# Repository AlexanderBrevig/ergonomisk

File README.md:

# Ergonomisk

My first ergogen experiment.

```
╭───╮ ╭───╮ ╭───╮ ╭───╮ ╭───╮ ╭───╮ ╭───╮ ╭───╮ ╭───╮ ╭───╮  
│ E │ │ r │ │ g │ │ o │ │ n │ │ o │ │ m │ │ i │ │ s │ │ k │  
╰───╯ ╰───╯ ╰───╯ ╰───╯ ╰───╯ ╰───╯ ╰───╯ ╰───╯ ╰───╯ ╰───╯  
```

## Install

* `git clone --recurse-submodules git@github.com:alexanderbrevig/ergonomisk`
* KiCAD 7
* `npm i -g ergogen`
* `make`

This will generate a stub PCB that I modified to get to the final design.

## REFs

https://splitkb.com/
https://fkcaps.com/?a=FlatFootFox
https://flatfootfox.com/ergogen-introduction/

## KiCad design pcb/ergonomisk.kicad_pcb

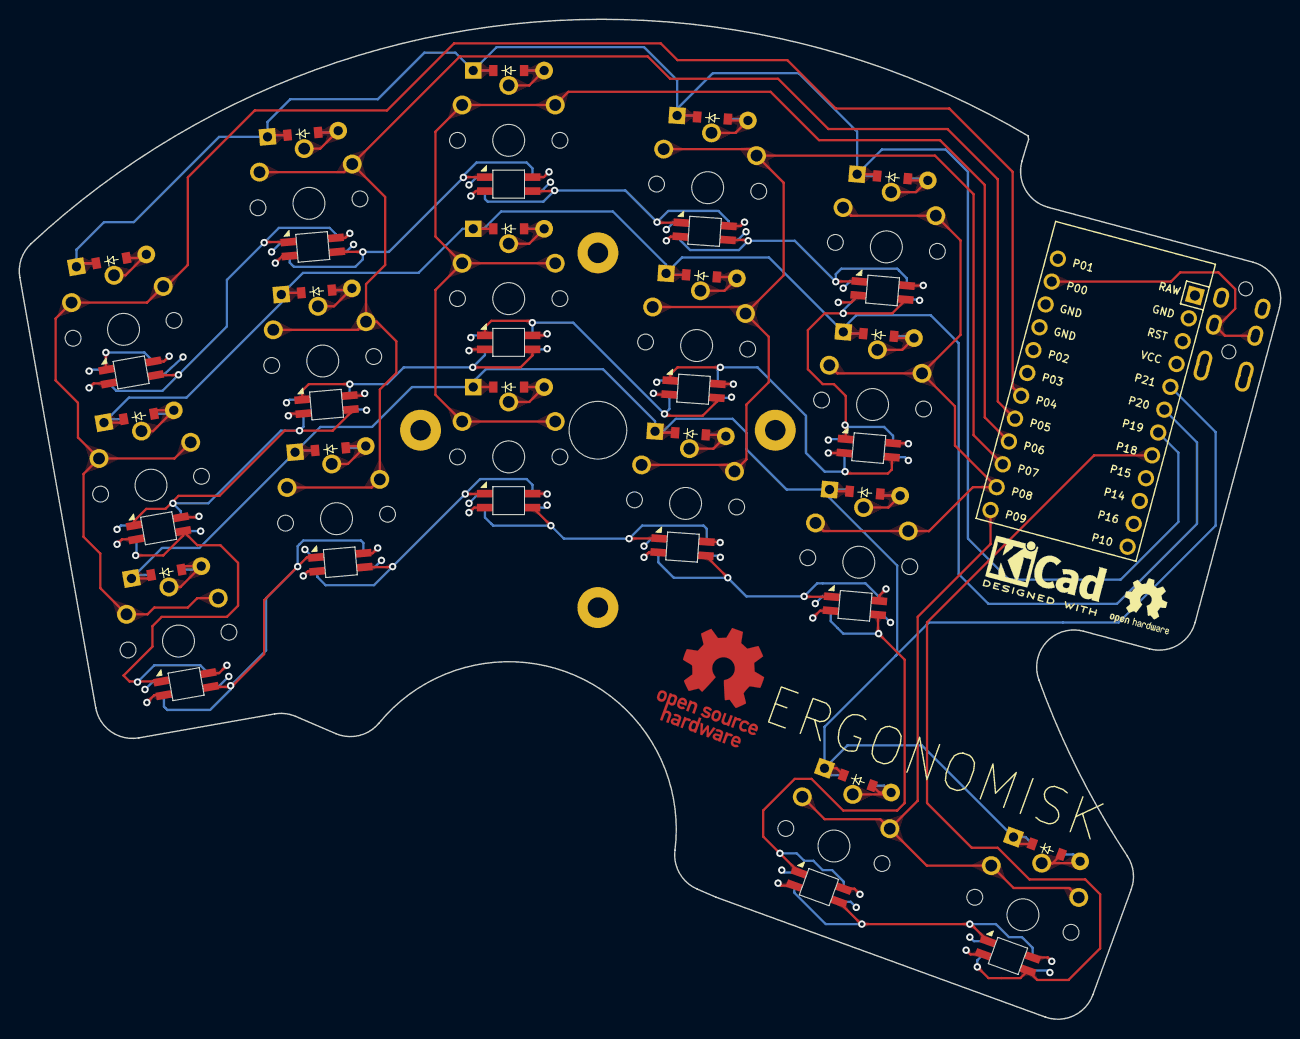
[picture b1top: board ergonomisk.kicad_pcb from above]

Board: 4 copper layers, 135.5 x 107.4 mm, 53 parts (0 on the bottom side), 46 nets.

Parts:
D1, D2, D3, D4, D5, D6, D7, D8, D9, D10, D11, D12, D13, D14, D15, D16, D17: ComboDiode
LED1, LED2, LED3, LED4, LED5, LED6, LED7, LED8, LED9, LED10, LED11, LED12, LED13, LED14, LED15, LED16, LED17: SK6812MINIE
MCU1: ProMicro
S1, S2, S3, S4, S5, S6, S7, S8, S9, S10, S11, S12, S13, S14, S15, S16, S17: PG1350
TRRS1: TRRS-PJ-320A-dual

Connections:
GND: LED1.3, LED2.3, LED3.3, LED4.3, LED5.3, LED6.3, LED7.3, LED8.3, LED9.3, LED10.3, LED11.3, LED12.3, LED13.3, LED14.3, LED15.3, LED16.3, LED17.3, MCU1.2, MCU1.15, MCU1.16, TRRS1.1, TRRS1.2
P0: MCU1.14, TRRS1.3
P4: MCU1.19, S1.1, S2.1, S3.1
P5: MCU1.20, S4.1, S5.1, S6.1
P6: MCU1.21, S7.1, S8.1, S9.1
P7: MCU1.22, S10.1, S11.1, S12.1
P8: MCU1.23, S13.1, S14.1, S15.1
P9: MCU1.24, S16.1, S17.1
P18: LED17.4, MCU1.8
P19: D3.1, D6.1, D9.1, D12.1, D15.1, MCU1.7
P20: D2.1, D5.1, D8.1, D11.1, D14.1, MCU1.6
P21: D1.1, D4.1, D7.1, D10.1, D13.1, D16.1, D17.1, MCU1.5
RAW: LED1.1, LED2.1, LED3.1, LED4.1, LED5.1, LED6.1, LED7.1, LED8.1, LED9.1, LED10.1, LED11.1, LED12.1, LED13.1, LED14.1, LED15.1, LED16.1, LED17.1, MCU1.1, TRRS1.4
bot_far_dout: LED10.4, LED13.2
bot_index_dout: LED7.4, LED10.2
bot_middle_dout: LED4.4, LED7.2
bot_pinky_dout: LED1.2, LED2.4
bot_ring_dout: LED1.4, LED4.2
far_bottom: D13.2, S13.2
far_home: D14.2, S14.2
far_top: D15.2, S15.2
home_far_dout: LED14.2, LED15.4
home_index_dout: LED11.2, LED14.4
home_middle_dout: LED8.2, LED11.4
home_pinky_dout: LED2.2, LED5.4
home_ring_dout: LED5.2, LED8.4
index_bottom: D10.2, S10.2
index_home: D11.2, S11.2
index_top: D12.2, S12.2
inner_keys: D16.2, S16.2
middle_bottom: D7.2, S7.2
middle_home: D8.2, S8.2
middle_top: D9.2, S9.2
outer_keys: D17.2, S17.2
pinky_bottom: D1.2, S1.2
pinky_home: D2.2, S2.2
pinky_top: D3.2, S3.2
ring_bottom: D4.2, S4.2
ring_home: D5.2, S5.2
ring_top: D6.2, S6.2
thumb_near_dout: LED13.4, LED16.2
thumb_outer_dout: LED16.4, LED17.2
top_far_dout: LED12.4, LED15.2
top_index_dout: LED9.4, LED12.2
top_middle_dout: LED6.4, LED9.2
top_ring_dout: LED3.4, LED6.2

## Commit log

2023-08-02 feat: initial design, not at all done
2023-08-02 fix: 3d model for choc and update pcb to use local footprint
2023-08-06 fix: close to first rev
2023-08-06 feat: add ergogen
2023-08-06 docs: fix clone with submods
2023-08-07 feat: getting close
2023-08-07 fix: updated ergogen
2023-08-07 fix: pre round save
2023-08-07 feat: ready for first order
2023-08-07 feat!: placed order
2023-08-07 chore: delete gerbs
2023-08-08 feat: add plate
2023-08-08 fix: JCL found an issue and I should've found it too
2023-08-22 docs: small edit
